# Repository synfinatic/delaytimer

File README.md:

# 12V/2A Delay Timer

## About

This is a simple adjustable power-off delay timer supporting 5-12V DC and
up to 2A.

When the power is turned on (both 12V and Switch are "on") then
Output is also on.  When Switch is "off", then a timer starts. When 
the timer expires (0-55 seconds) then Output is turned off.

## Specs
 * Voltage: 5-12VDC
 * Max Switched Current: 2A @ 12V
 * Delay: 0-55 seconds 
 * Power requirements when running: 5ma @ 12V
 * Power requrements when turned off: 0ma

## Connections

 * GND - Ground
 * 5-12V - Unswitched 5-12V DC power
 * Switch - Switched 5-12V DC power
 * Output - 2A/5-12V DC delayed power off

## Project Files

 * kicad - [KiCad](http://kicad-pcb.org/) 4.x design files
 * ltspice - [LTSpice](http://www.linear.com/designtools/software/) simulation 

## License and Copyright

Copyright 2017 Aaron Turner

This project is licensed under the [GPLv3](https://www.gnu.org/licenses/gpl-3.0.en.html).

## References

Special thanks to [Rob Paisley](http://home.cogeco.ca/~rpaisley4/LM555.html#30) who helped with the circuit design.

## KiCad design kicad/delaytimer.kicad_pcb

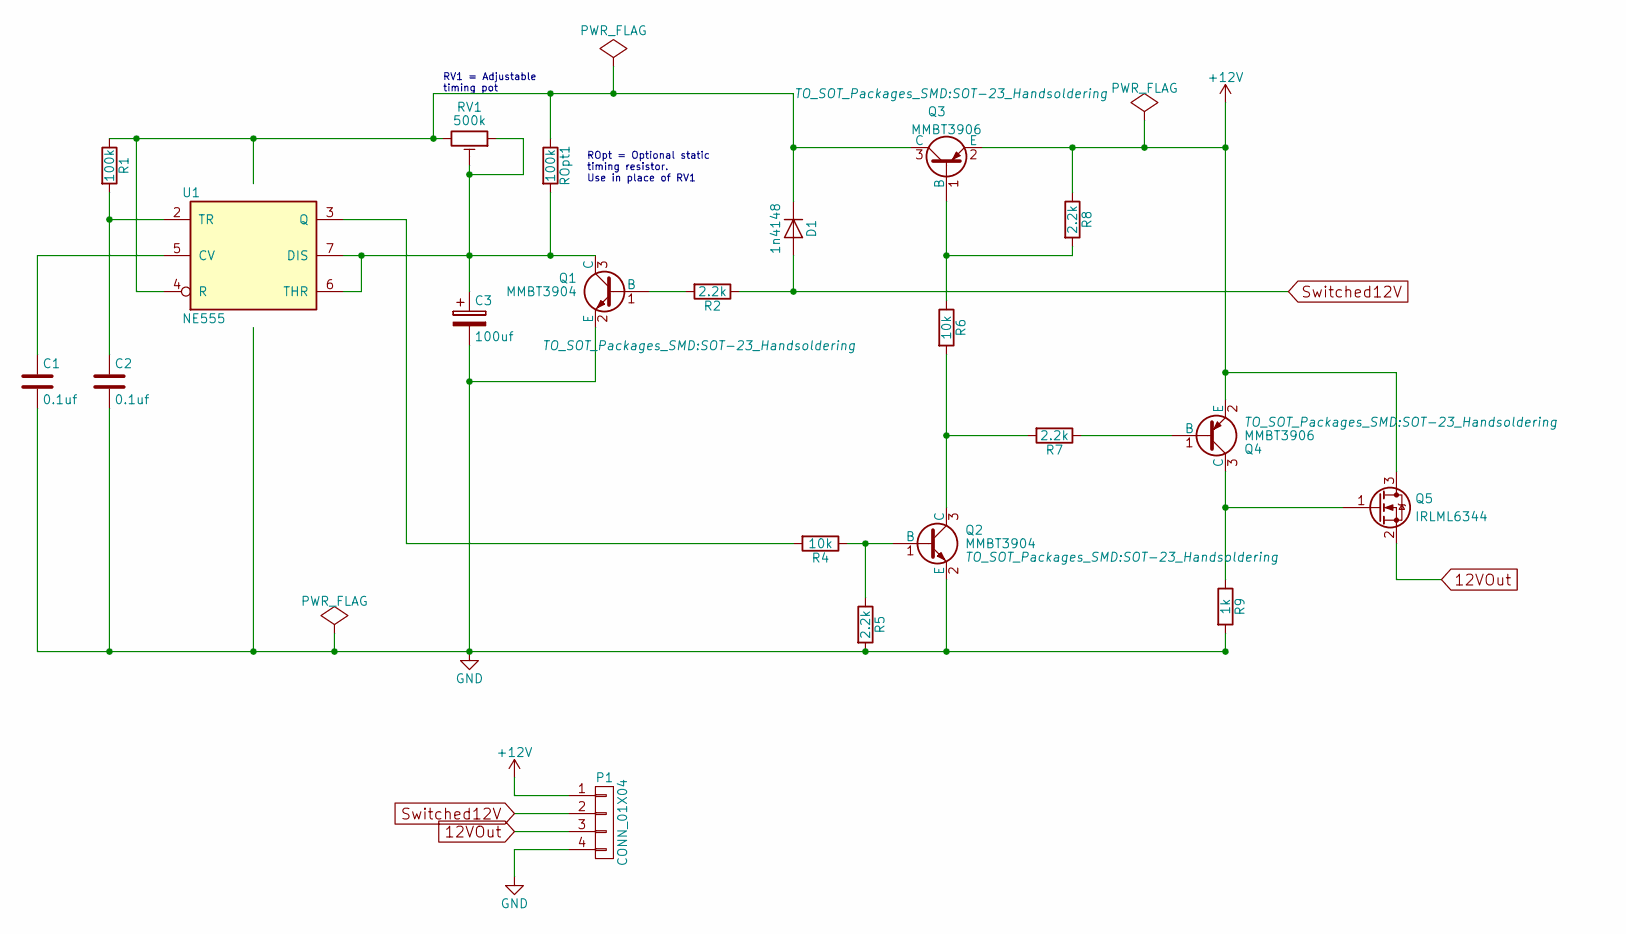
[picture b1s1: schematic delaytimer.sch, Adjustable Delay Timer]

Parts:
C1, C2: 0.1uf; C_0805_HandSoldering
C3: 100uf; c_elec_6.3x7.7
D1: 1n4148; SOD-123
P1: CONN_01X04; TerminalBlock_Pheonix_PT-3.5mm_4pol
Q1, Q2: MMBT3904; SOT-23_Handsoldering
Q3, Q4: MMBT3906; SOT-23_Handsoldering
Q5: IRLML6344; SOT-23_Handsoldering
R1: 100k; R_0805_HandSoldering
R2, R5, R7, R8: 2.2k; R_0805_HandSoldering
R4, R6: 10k; R_0805_HandSoldering
R9: 1k; R_0805_HandSoldering
ROpt1: 100k; R_0805_HandSoldering
RV1: 500k; Potentiometer_Bourns_3296W_3-8Zoll_Inline_ScrewUp
U1: NE555; SOIC-8_3.9x4.9mm_Pitch1.27mm

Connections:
12VOut: P1.3, Q5.2 (S)
+12V: P1.1, Q3.2 (E), Q4.2 (E), Q5.3 (D), R8.1
GND: C1.2, C2.2, C3.2, P1.4, Q1.2 (E), Q2.2 (E), R5.2, R9.2, U1.1 (GND)
unnamed: C1.1, U1.5 (CV)
unnamed: C2.1, R1.2, U1.2 (TR)
unnamed: C3.1, Q1.3 (C), ROpt1.2, RV1.1, RV1.2, U1.6 (THR), U1.7 (DIS)
unnamed: Q1.1 (B), R2.2
unnamed: Q2.1 (B), R4.1, R5.1
unnamed: Q2.3 (C), R6.2, R7.2
unnamed: Q3.1 (B), R6.1, R8.2
unnamed: Q4.1 (B), R7.1
unnamed: Q4.3 (C), Q5.1 (G), R9.1
unnamed: R4.2, U1.3 (Q)
Switched12V: D1.2 (A), P1.2, R2.1
VCC: D1.1 (K), Q3.3 (C), R1.1, ROpt1.1, RV1.3, U1.4 (R), U1.8 (VCC)

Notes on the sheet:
ROpt = Optional static timing resistor. Use in place of RV1
RV1 = Adjustable timing pot

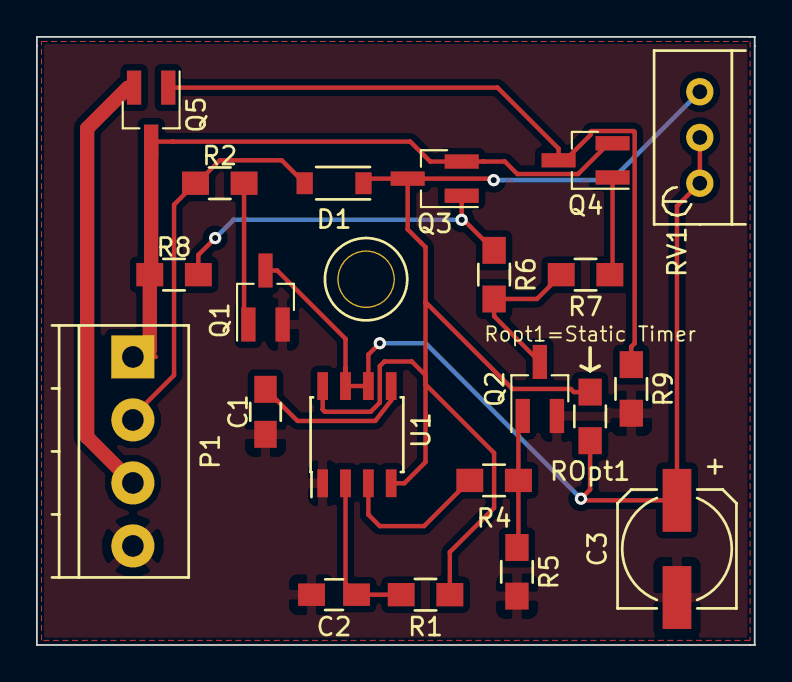
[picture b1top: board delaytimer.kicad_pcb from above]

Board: 2 copper layers, 39.9 x 33.8 mm, 21 parts (0 on the bottom side), 15 nets.

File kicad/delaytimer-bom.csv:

Source,/Users/aturner/GIT/delaytimer/kicad/delaytimer.sch
Kicad Rev,Eeschema 4.0.5
Generated Date,Sunday, March 05, 2017 'AMt' 10:22:40 AM

Title,Adjustable Delay Timer
Company,Aaron Turner <synfinatic@gmail.com>
Revision,v1.1
Date Issue,2017-03-05
Comment,https://synfin.net/delaytimer
Comment,Supports 0-55 second delay
Comment,Use to add an adjustible power off delay for 12V applications

Reference,Value,Library,Library Ref
U1,NE555,linear,NE555
RV1,500k,device,POT_TRIM
Q3,MMBT3906,transistors,MMBT3906
Q4,MMBT3906,transistors,MMBT3906
Q1,MMBT3904,transistors,MMBT3904
Q2,MMBT3904,transistors,MMBT3904
C1,0.1uf,device,C
R1,100k,device,R
C3,100uf,device,CP
R2,2.2k,device,R
D1,1n4148,device,D
R8,2.2k,device,R
R6,10k,device,R
R7,2.2k,device,R
R4,10k,device,R
R5,2.2k,device,R
C2,0.1uf,device,C
Q5,IRLML6344,device,Q_NMOS_GSD
R9,1k,device,R
P1,CONN_01X04,conn,CONN_01X04
ROpt1,100k,device,R

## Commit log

2017-02-18 Initial checkin
    Contains:
    - LTSpice design showing the circuit should work
    - First pass at KiCad design for the actual PCB
2017-02-19 Update schema / pcb / readme
    - Removed unneeded resistor
    - Reduce vias
    - Fix labels for header
    - Added copper pour on front/back
    - UpdatedBOM
    - Added Makefile for building BOM CSV
2017-02-22 Add static resistor option in place of pot
    - Added a static resistor (ROpt) so you can save on the price of a pot
    - Added measurements to the board for making an enclosure
2017-02-24 ignore KiCad's autosave created files
2017-03-05 add updated BOM
2017-03-05 Update to v1.1
    - Fix Q1,Q4 which were connected wrong
    - Fix routing of GND to use GND plane
